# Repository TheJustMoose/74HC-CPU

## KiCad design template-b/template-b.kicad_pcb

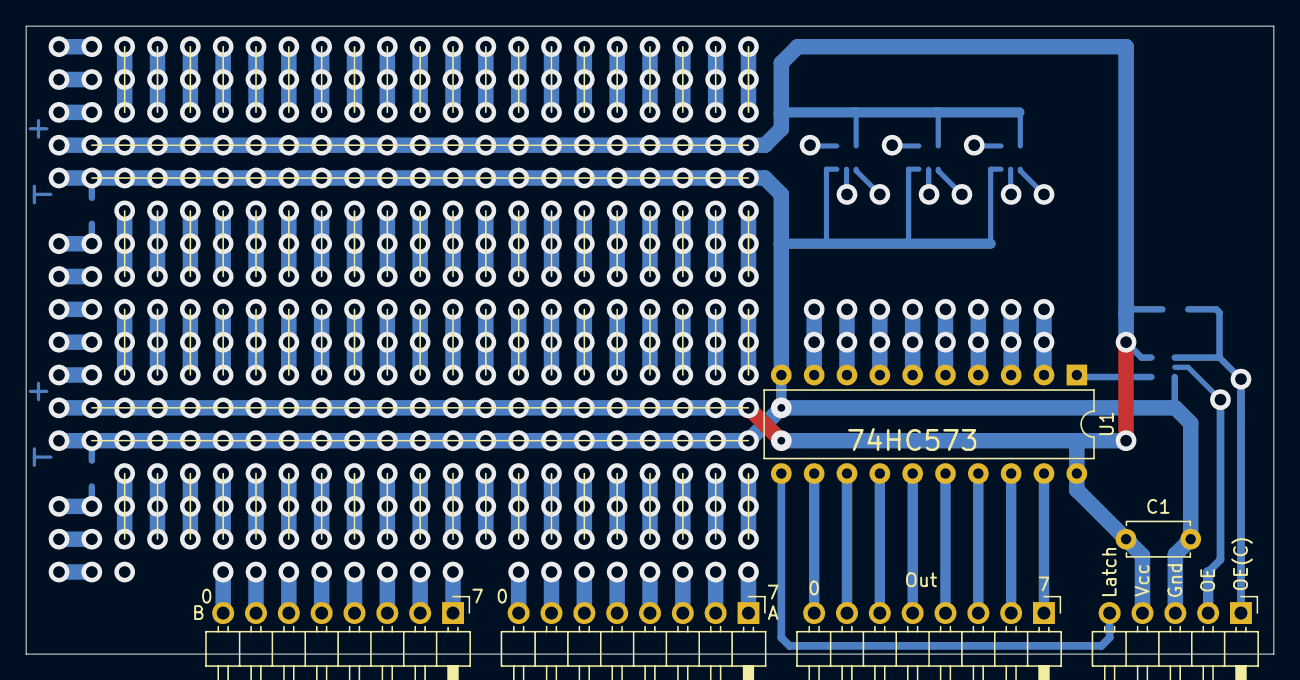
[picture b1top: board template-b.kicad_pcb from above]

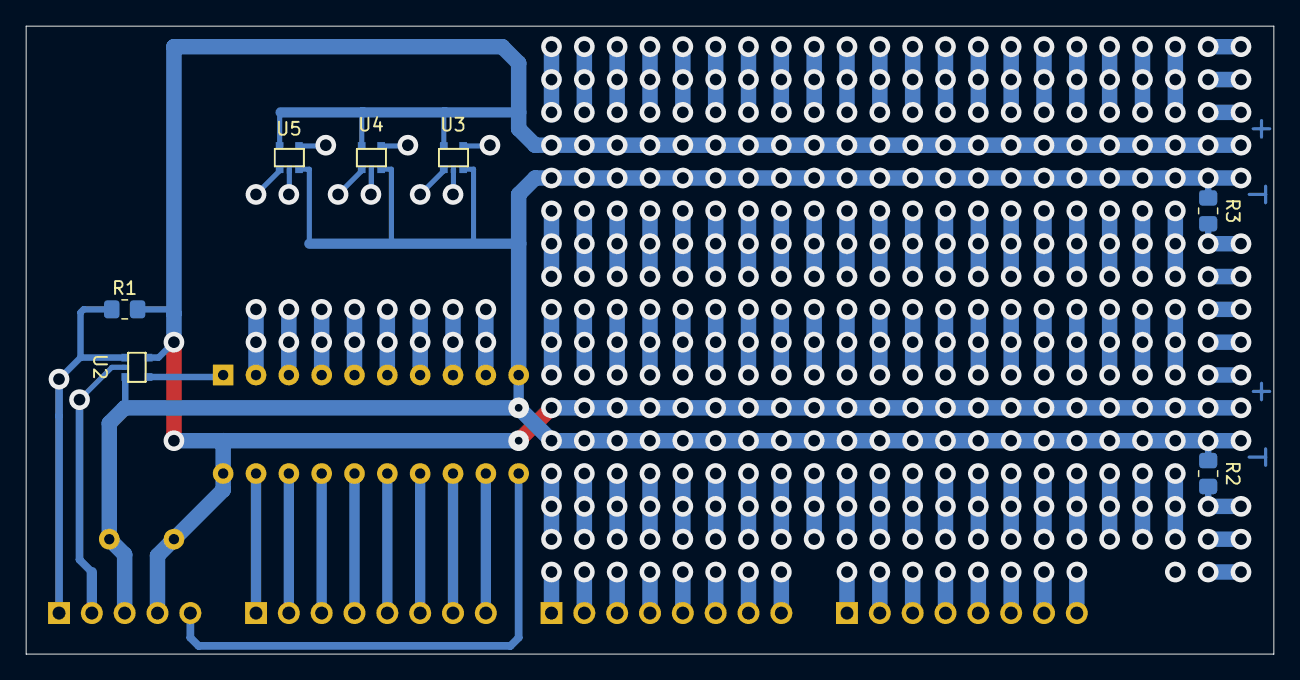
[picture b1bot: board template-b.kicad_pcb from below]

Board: 2 copper layers, 96.5 x 48.6 mm, 13 parts (7 on the bottom side), 14 nets.

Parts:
C1: 0.1uF; C_Disc_D4.7mm_W2.5mm_P5.00mm
J1, J2, J3: Conn_01x08_Male; PinHeader_1x08_P2.54mm_Horizontal
J4: Conn_01x05_Male; PinHeader_1x05_P2.54mm_Horizontal
R1: 10k; R_0805_2012Metric_Pad1.20x1.40mm_HandSolder
R2, R3: R; R_0805_2012Metric_Pad1.20x1.40mm_HandSolder
U1: 74LS573; DIP-20_W7.62mm
U2, U3, U4, U5: 74AHC1G08; tssop5

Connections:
GND: C1.2, J4.3, R2.2, R3.2, U1.10, U2.3, U3.3, U4.3, U5.3
unnamed: J3.1, U1.19
unnamed: J3.2, U1.18
unnamed: J3.3, U1.17
unnamed: J3.4, U1.16
unnamed: J3.5, U1.15
unnamed: J3.6, U1.14
unnamed: J3.7, U1.13
unnamed: J3.8, U1.12
unnamed: J4.1, R1.1, U2.1
unnamed: J4.2, U2.2
unnamed: J4.5, U1.11
unnamed: U1.1, U2.4
VCC: C1.1, J4.4, R1.2, U1.20, U2.5, U3.5, U4.5, U5.5
